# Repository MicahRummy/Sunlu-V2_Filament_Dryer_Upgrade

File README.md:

# Sunlu-V2_Filament_Dryer_Upgrade
 Upgraded the Sunlu PCB and Firmware.

I had to redesign the cover on the orginal design, and cut a hole for the inductor and aliminum capacitor which didn't fit in the original enclosure. I used the wrong JST connectors, so I had to cut a hole for those as well, but that can be avoided with horizontal connectors instead of vertical. I provided all the design files and Code. The PCB, Schematic, and cover were designed inside Fusion 360. I used a generic OLED display, which I got off of amazon, link below. Most other components can be found in the BOD.csv.

UCTRONICS 0.96 Inch OLED Module... https://www.amazon.com/dp/B072Q2X2LL?ref=ppx_pop_mob_ap_share

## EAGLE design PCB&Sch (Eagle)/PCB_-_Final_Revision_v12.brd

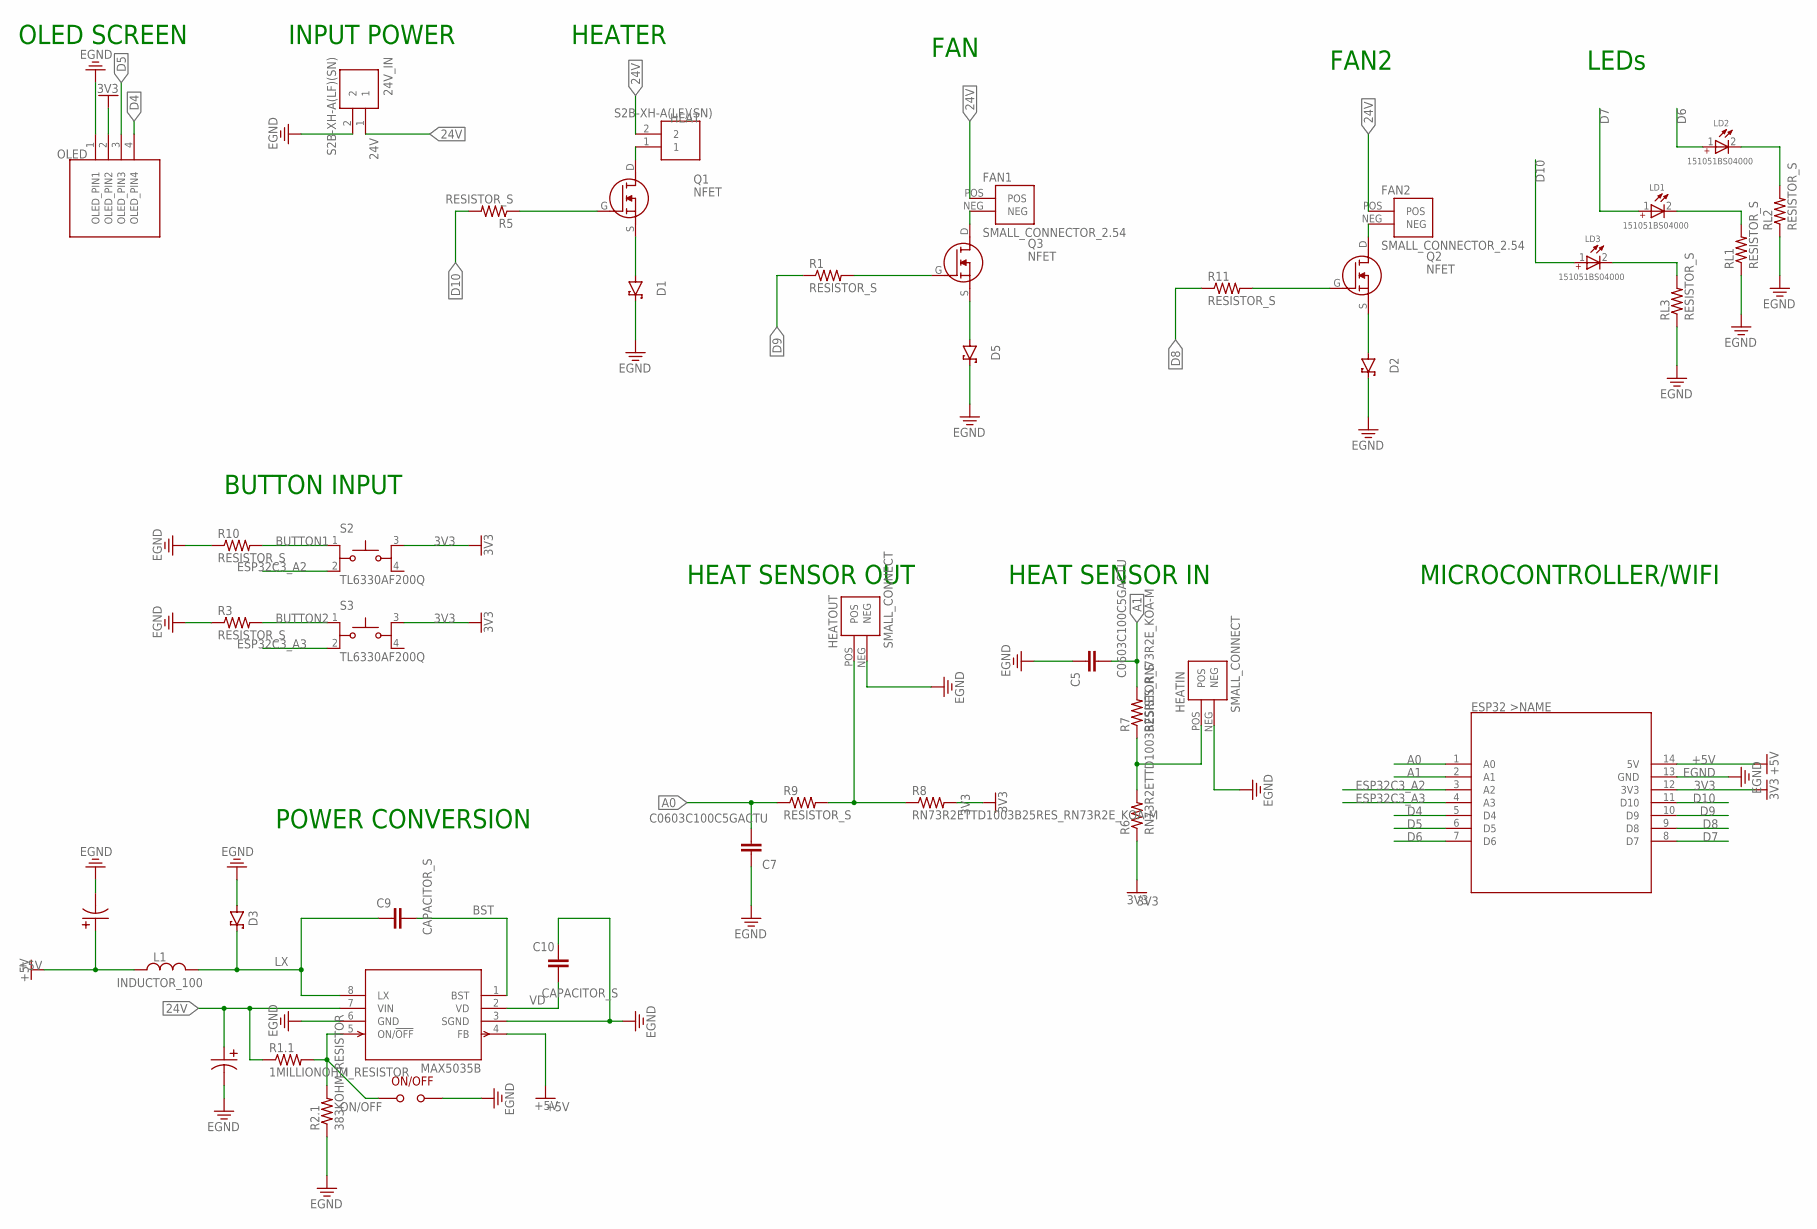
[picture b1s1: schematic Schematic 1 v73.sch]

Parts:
24V_IN: S2B-XH-A(LF)(SN); HDR-02/RA
C5, C7: C0603C100C5GACTU; CAP_0603
C9, C10: CAPACITOR_S; CAPACITOR_M
D1, D2, D5: ES1D; SCHOTTKY_DIODE_S
D3: MBR0520LT1G; PANJIT_SB52AFC~SB56AFC_SERIES_DIODE
ESP32C3: XIAO_ESP32C3_ALT; XIIO_ESP32C3_ALT
FAN1, FAN2: SMALL_CONNECTOR_2.54; SMALL_CONNECT2.54
HEAT: S2B-XH-A(LF)(SN); HDR-02/RA
HEATIN: SMALL_CONNECT
HEATOUT: SMALL_CONNECT
L1: INDUCTOR_100; 100UH_INDUCTOR
LD1, LD2, LD3: 151051BS04000; WL-TMRC_5MM
OLED: I2C_OLED
ON/OFF: SOLDER_JUMPER
PC1: POLORIZED_100UF; TANTALUM_CAPACITOR_68UF
PC2: 68UF_POLORIZED_CAP; 68UF_CAPAE830X1000N
Q1, Q2, Q3: NFET
R1, R3, R5, R7, R9, R10, R11: RESISTOR_S
R1.1: 1MILLIONOHM_RESISTOR; 1MOHM_RESISTOR_SMD
R2.1: 383KOHM_RESISTOR; 383KOHM_RESISTOR_0805
R6, R8: RN73R2ETTD1003B25RES_RN73R2E_KOA-M; RES_RN73R2E_KOA-M
RL1, RL2, RL3: RESISTOR_S
S2, S3: TL6330AF200Q; SW_TL6330AF200Q
U1: MAX5035BASA+T; 21-0041B_8_MXM-M

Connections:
3V3: ESP32C3.12 (3V3), OLED.2 (OLED_PIN2), R6.2, R8.1, S2.3, S3.3
24V: 24V_IN.1, FAN1.POS, FAN2.POS, HEAT.2, PC2.POS, R1.1.2, U1.7 (VIN)
+5V: ESP32C3.14 (5V), L1.P$1 (1), PC1.+ (POS), U1.4 (FB)
A0: C7.2, ESP32C3.1 (A0), R9.2
A1: C5.2, ESP32C3.2 (A1), R7.1
BST: C9.2, U1.1 (BST)
BUTTON1: R10.1, S2.1
BUTTON2: R3.1, S3.1
D4: ESP32C3.5 (D4), OLED.4 (OLED_PIN4)
D5: ESP32C3.6 (D5), OLED.3 (OLED_PIN3)
D6: ESP32C3.7 (D6), LD2.1 (+)
D7: ESP32C3.8 (D7), LD1.1 (+)
D8: ESP32C3.9 (D8), R11.2
D9: ESP32C3.10 (D9), R1.2
D10: ESP32C3.11 (D10), LD3.1 (+), R5.1
DRAIN1: HEAT.1, Q1.D
DRAIN2: FAN1.NEG, Q3.D
DRAIN3: FAN2.NEG, Q2.D
EGND: 24V_IN.2, C5.1, C7.1, C10.1, D1.NEG, D2.NEG, D3.POS, D5.NEG, ESP32C3.13 (GND), HEATIN.NEG, HEATOUT.NEG, OLED.1 (OLED_PIN1), ON/OFF.P$2, PC1.- (NEG), PC2.NEG, R2.1.2, R3.2, R10.2, RL1.2, RL2.2, RL3.2, U1.3 (SGND), U1.6 (GND)
ESP32C3_A2: ESP32C3.3 (A2), S2.2
ESP32C3_A3: ESP32C3.4 (A3), S3.2
GATE1: Q1.G, R5.2
GATE2: Q3.G, R1.1
GATE3: Q2.G, R11.1
HEAT_IN: HEATIN.POS, R6.1, R7.2
HEAT_OUT: HEATOUT.POS, R8.2, R9.1
LX: C9.1, D3.NEG, L1.P$2 (2), U1.8 (LX)
ON/OFF: ON/OFF.P$1, R1.1.1, R2.1.1, U1.5 (ON/!OFF)
RL1: LD1.2 (-), RL1.1
RL2: LD2.2 (-), RL2.1
RL3: LD3.2 (-), RL3.1
SOURCE1: D1.POS, Q1.S
SOURCE2: D5.POS, Q3.S
SOURCE3: D2.POS, Q2.S
VD: C10.2, U1.2 (VD)

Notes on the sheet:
POWER CONVERSION
INPUT POWER
OLED SCREEN
HEAT SENSOR IN
HEAT SENSOR OUT
HEATER
FAN
MICROCONTROLLER/WIFI
BUTTON INPUT
FAN2
LEDs

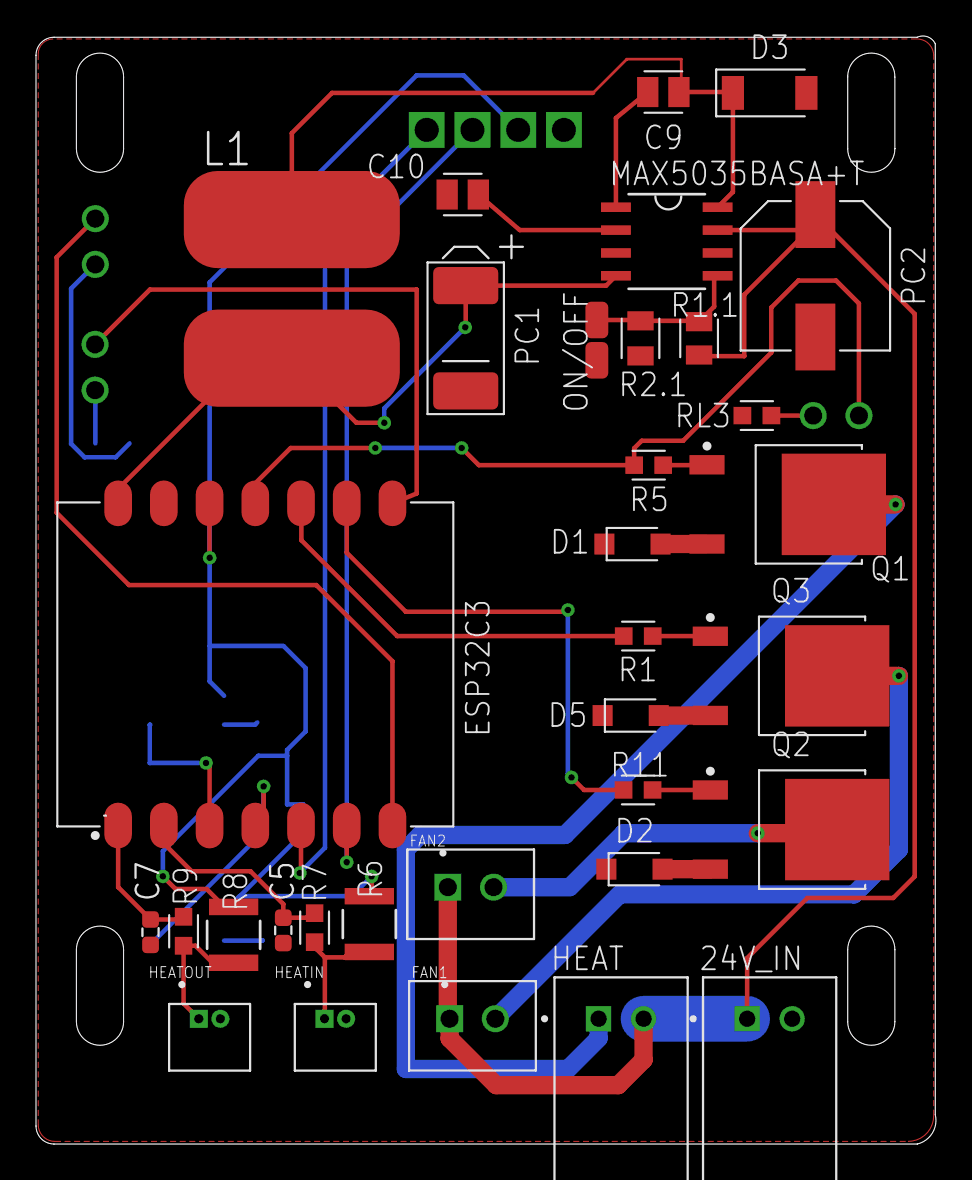
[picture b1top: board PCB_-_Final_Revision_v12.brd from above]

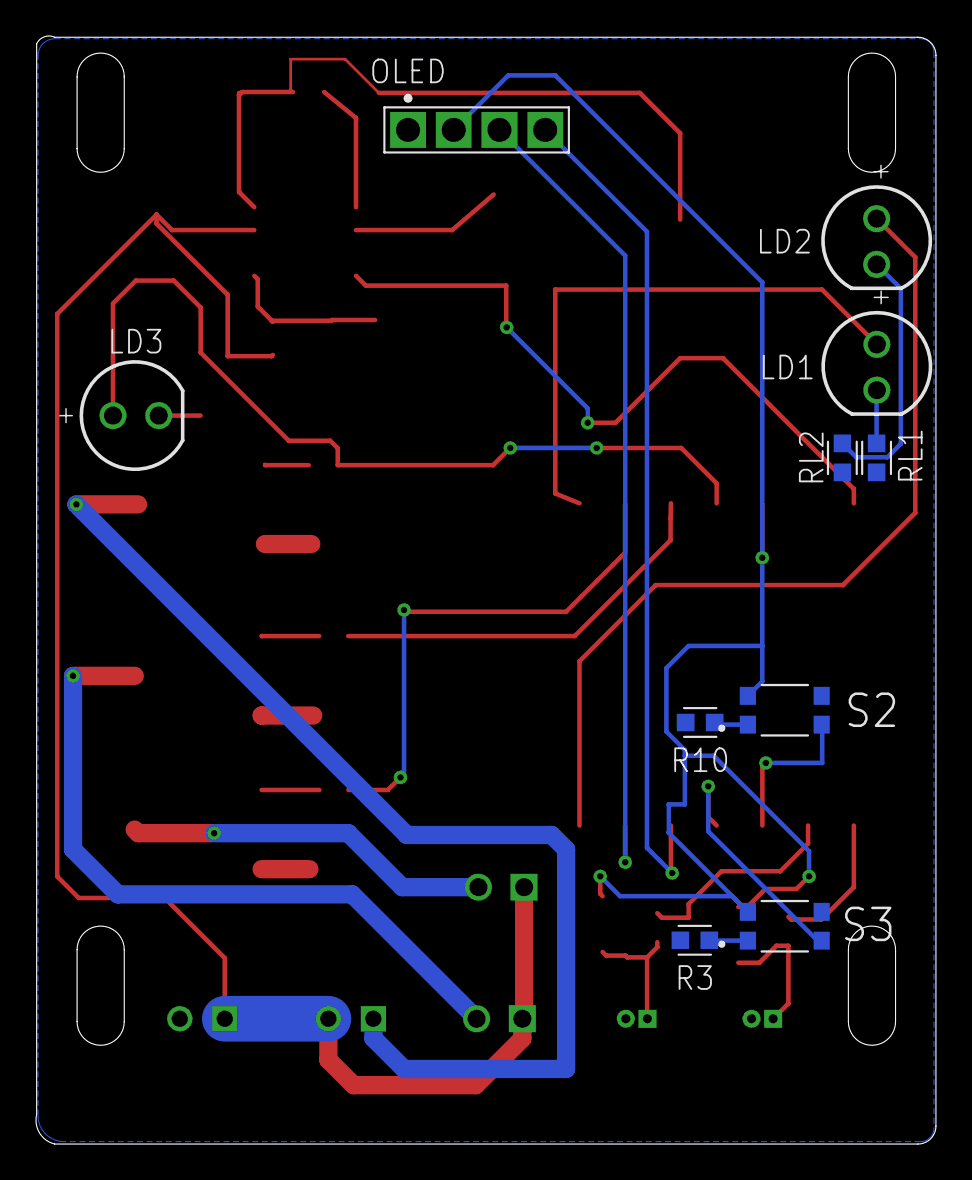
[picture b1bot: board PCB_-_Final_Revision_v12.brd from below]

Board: 2 copper layers, 50.0 x 61.6 mm, 43 parts (10 on the bottom side), 35 nets.

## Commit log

2023-08-10 Update README.md
    Added a more detailed description.
2023-08-10 Update README.md
    fixed Typos

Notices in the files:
parts and their libraries:
Wurth_LEDs_WL-TMRC: Copyright: Würth Elektronik
COPYRIGHT: Copyright (C) 2022 Ultra Librarian. All rights reserved.
